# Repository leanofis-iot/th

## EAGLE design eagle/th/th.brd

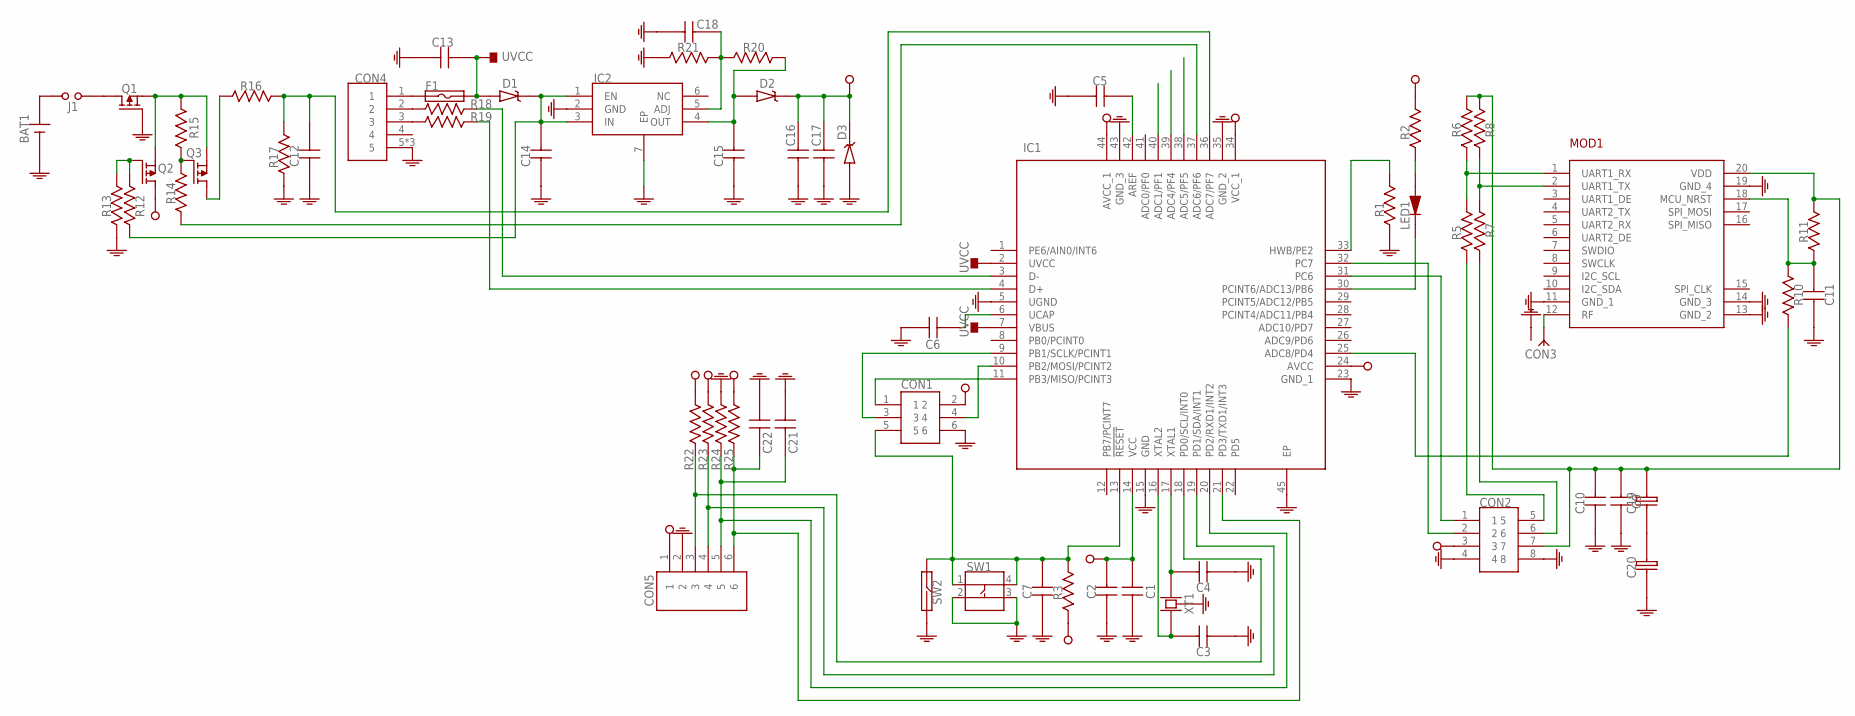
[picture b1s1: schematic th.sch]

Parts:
BAT1: 211P-C-HOLDER
C1, C2, C3, C4, C5, C6, C7, C9, C10, C11, C12, C13, C16, C17, C18, C21, C22: CAPACITOR-0603; 0603
C14, C15: CAPACITOR-0805; 0805
C19, C20: CAPACITOR-8-3.5
CON1: ISP
CON2: HEADER-8P-2R-DIP-2_54MM
CON3: SMA-RF
CON4: USB-MICRO-DIP-VER
CON5: HEADER-6P-DIP-2_54MM
D1, D2: DIODE-SCHOTTKY; SOD123-DIODE
D3: ZENER-SOD123; SOD123-DIODE
F1: FUSE-1206; 1206
IC1: ATMEGA32U4-MU; QFN-44
IC2: MIC5219-ADJ-TDFN-6; TDFN-6
J1: JUMPER; HEADER-2P-DIP-2_54MM
LED1: LED-0805; 0805-LED
MOD1: RAK4200
Q1, Q2, Q3: P-MOSFET; SOT23-3
R1, R2, R3, R5, R6, R7, R8, R10, R11, R12, R13, R14, R15, R16, R17, R18, R19, R20, R21, R22, R23, R24, R25: RESISTOR-0603; 0603
SW1: BUTTON-4P-SMD-5X5
SW2: REED-DIP
XT1: CRYSTAL-5032-4P

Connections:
GND: BAT1.2 (-), C1.1, C2.1, C3.1, C4.1, C5.1, C6.1, C7.1, C9.1, C10.1, C11.1, C12.1, C13.1, C14.1, C15.1, C16.1, C17.1, C18.1, C20.P$1 (1), C21.1, C22.1, CON1.6, CON2.4, CON2.8, CON3.2 (GND), CON3.3 (GND), CON3.4 (GND), CON3.5 (GND), CON4.5, CON4.6 (5), CON4.7 (5), CON5.2, D3.2 (A), IC1.5 (UGND), IC1.15 (GND), IC1.23 (GND_1), IC1.35 (GND_2), IC1.43 (GND_3), IC1.45 (EP), IC2.2 (GND), IC2.7 (EP), MOD1.11 (GND_1), MOD1.13 (GND_2), MOD1.14 (GND_3), MOD1.19 (GND_4), Q1.1 (G), R1.1, R13.1, R17.1, R21.1, R24.1, SW1.2, SW1.3, SW2.P$2 (2), XT1.2 (GND), XT1.4 (GND)
unnamed: C7.2, CON1.5, IC1.13 (!RESET), R3.2, SW1.1, SW1.4, SW2.P$1 (1)
unnamed: C11.2, MOD1.18 (MCU_NRST), R10.1, R11.1
unnamed: CON1.1, IC1.11 (PB3/MISO/PCINT3)
unnamed: CON3.1 (ANT), MOD1.12 (RF)
unnamed: J1.1, Q1.3 (D)
unnamed: MOD1.1 (UART1_RX), R5.2, R6.1
unnamed: MOD1.2 (UART1_TX), R7.2, R8.1
unnamed: BAT1.1 (+), J1.2 (3)
unnamed: CON1.4, IC1.10 (PB2/MOSI/PCINT2)
unnamed: C3.2, IC1.16 (XTAL2), XT1.1
unnamed: CON2.1, IC1.31 (PC6)
unnamed: C4.2, IC1.17 (XTAL1), XT1.3 (2)
unnamed: C9.2, C10.2, C19.P$2 (2), CON2.7, MOD1.20 (VDD), R6.2, R8.2, R11.2
unnamed: CON2.6, R7.1
unnamed: C18.2, IC2.5 (ADJ), R20.2, R21.2
unnamed: IC1.25 (ADC8/PD4), R10.2
unnamed: C21.2, CON5.5, IC1.20 (PD2/RXD1/INT2), R24.2
unnamed: C22.2, CON5.6, IC1.21 (PD3/TXD1/INT3), R25.2
unnamed: IC1.30 (PCINT6/ADC13/PB6), LED1.1 (K)
unnamed: C19.P$1 (1), C20.P$2 (2)
unnamed: CON2.2, IC1.32 (PC7)
unnamed: C5.2, IC1.42 (AREF)
unnamed: Q3.1 (G), R14.2, R15.2
unnamed: CON4.1, F1.1
unnamed: C6.2, IC1.6 (UCAP)
unnamed: LED1.2 (A), R2.1
unnamed: C12.2, IC1.36 (ADC7/PF7), R16.2, R17.2
unnamed: C14.2, D1.1 (K), IC2.1 (EN), IC2.3 (IN), R12.1
unnamed: C15.2, D2.2 (A), IC2.4 (OUT), R20.1
unnamed: CON4.2, R18.1
unnamed: CON4.3, R19.1
unnamed: IC1.3 (D-), R18.2
unnamed: IC1.4 (D+), R19.2
unnamed: CON1.3, IC1.9 (PB1/SCLK/PCINT1)
unnamed: IC1.37 (ADC6/PF6), R14.1
unnamed: Q2.1 (G), R12.2, R13.2
unnamed: Q1.2 (S), Q2.2 (S), Q3.2 (S), R15.1
unnamed: Q3.3 (D), R16.1
unnamed: CON2.5, R5.1
unnamed: IC1.33 (HWB/PE2), R1.2
unnamed: CON5.3, IC1.18 (PD0/SCL/INT0), R22.2
unnamed: CON5.4, IC1.19 (PD1/SDA/INT1), R23.2
UVCC: C13.2, D1.2 (A), F1.2, IC1.2 (UVCC), IC1.7 (VBUS)
VCC: C1.2, C2.2, C16.2, C17.2, CON1.2, CON2.3, CON5.1, D2.1 (K), D3.1 (K), IC1.14 (VCC), IC1.24 (AVCC), IC1.34 (VCC_1), IC1.44 (AVCC_1), Q2.3 (D), R2.2, R3.1, R22.1, R23.1, R25.1

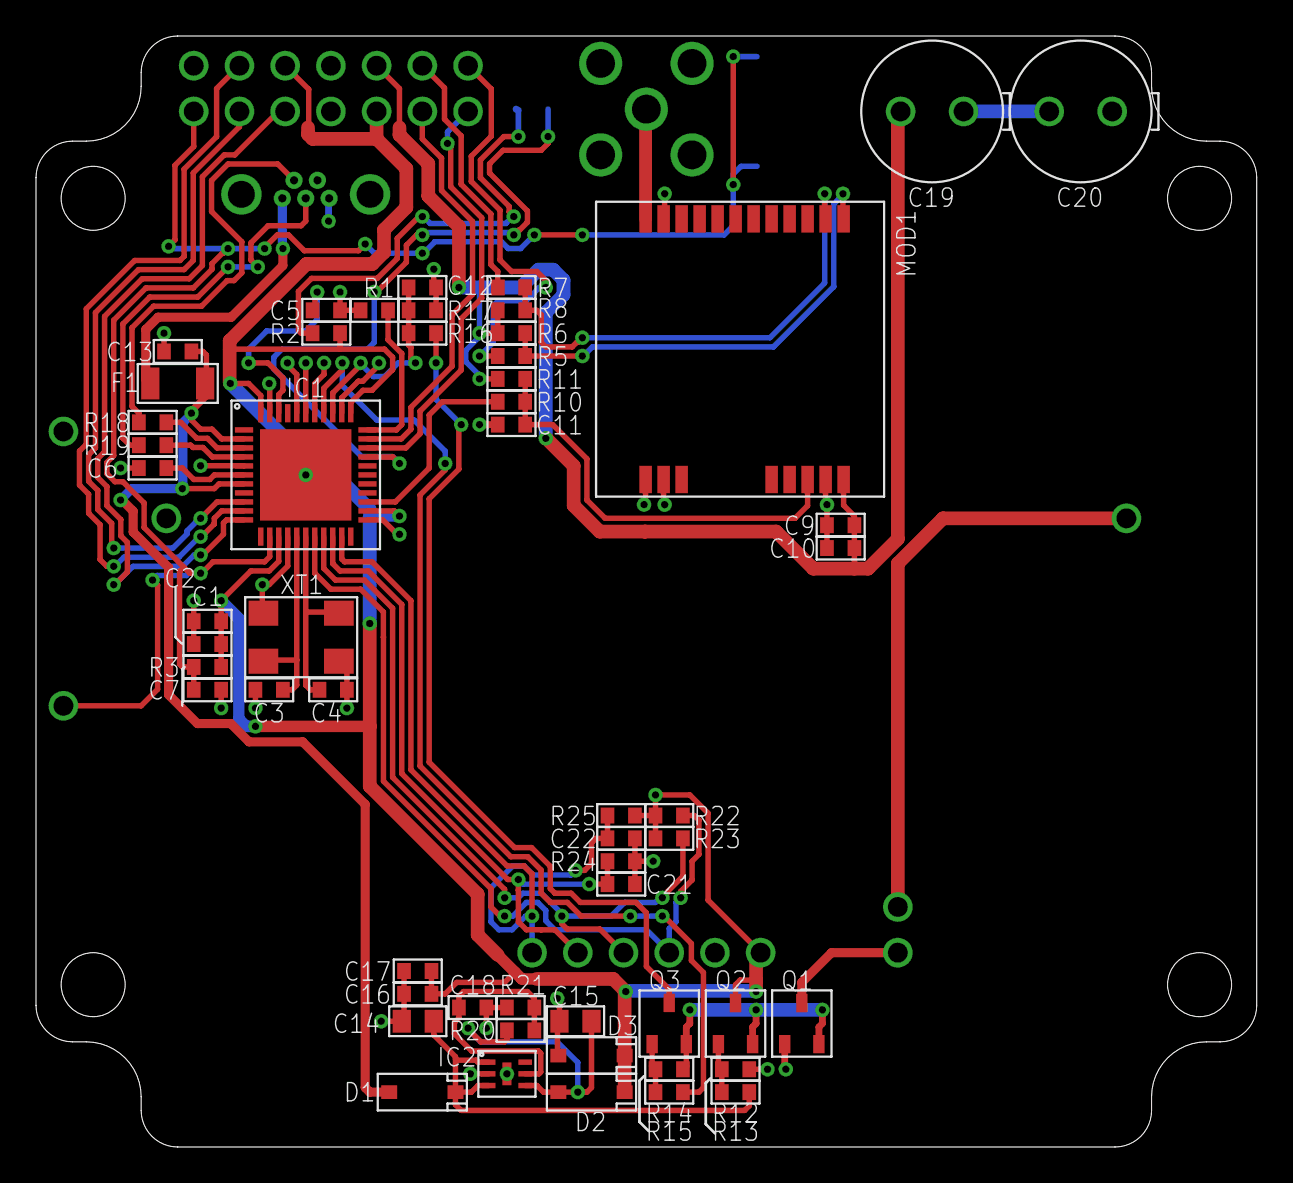
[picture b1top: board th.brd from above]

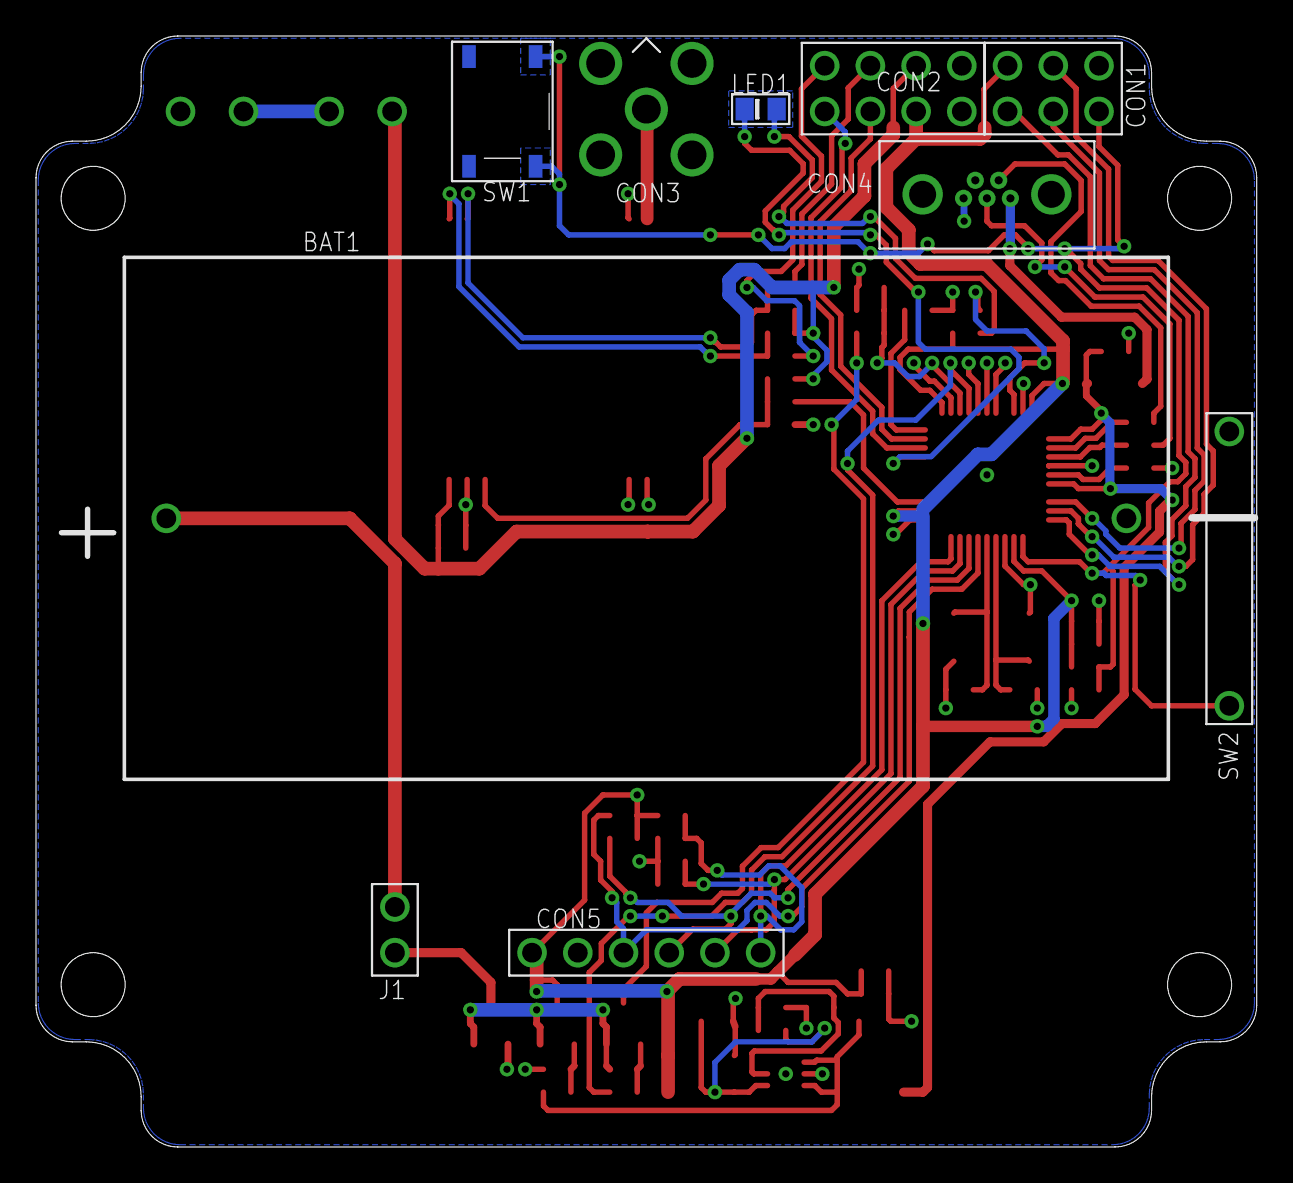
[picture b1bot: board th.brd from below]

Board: 2 copper layers, 67.8 x 61.7 mm, 65 parts (10 on the bottom side), 45 nets.
